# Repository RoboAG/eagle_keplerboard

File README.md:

# keplerboard
Circuit for simple robots.

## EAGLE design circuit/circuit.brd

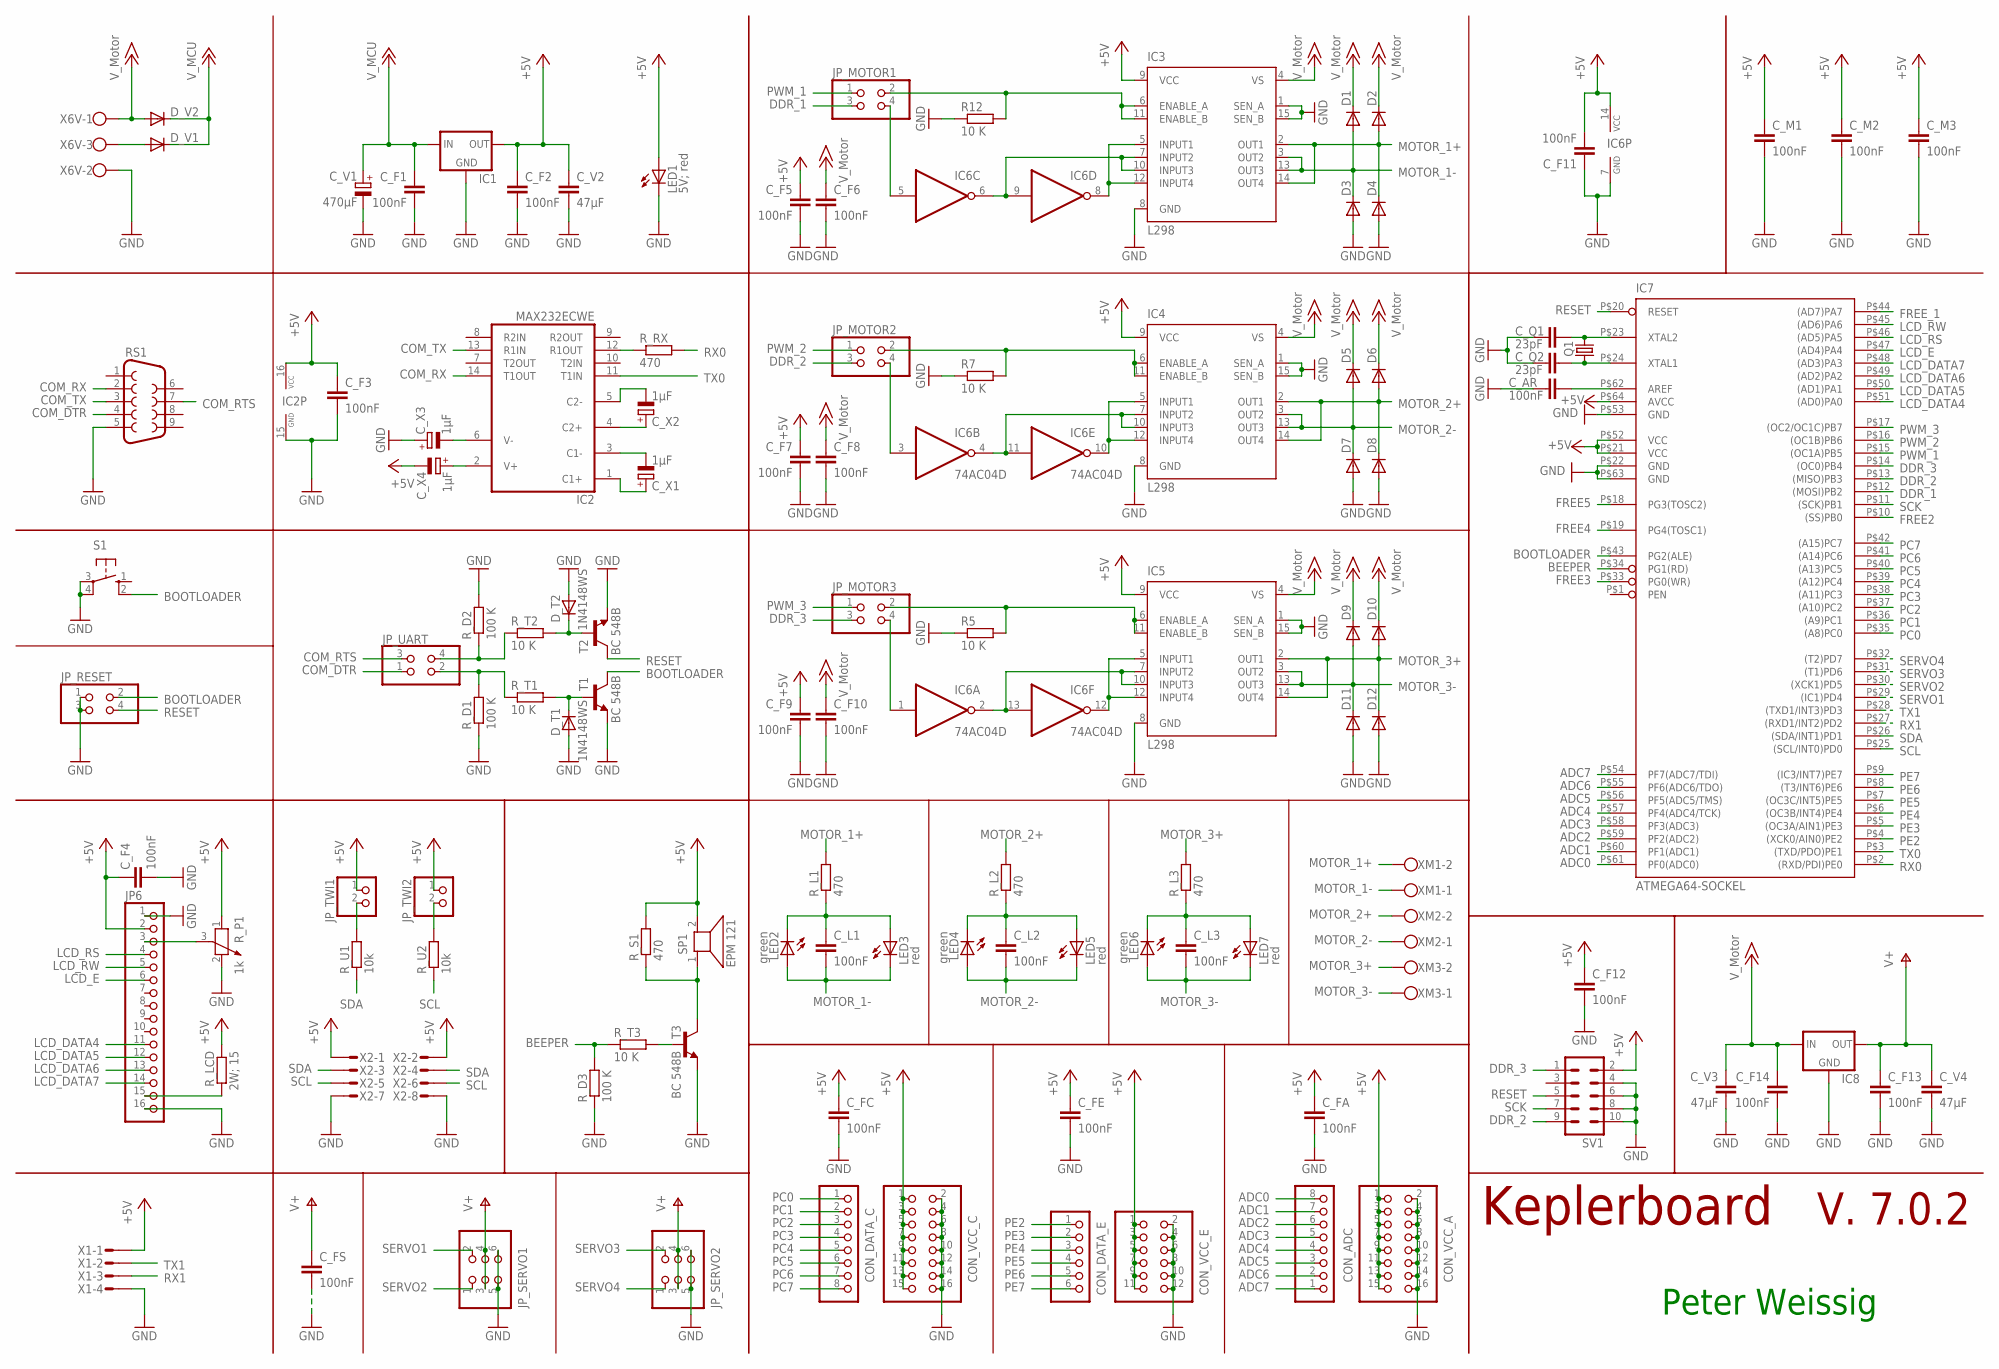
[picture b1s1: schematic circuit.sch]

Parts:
CON_ADC: PINHD-1X8; 1X08
CON_DATA_C: PINHD-1X8; 1X08
CON_DATA_E: PINHD-1X6; 1X06
CON_VCC_A: PINHD-2X8; 2X08
CON_VCC_C: PINHD-2X8; 2X08
CON_VCC_E: PINHD-2X6; 2X06
C_AR: 100nF; C025-025X050
C_F1, C_F2, C_F3, C_F5, C_F6, C_F7, C_F8, C_F9, C_F10, C_F11, C_F12, C_F13, C_F14: 100nF; C1206K
C_F4: 100nF; C025-025X050
C_FA: 100nF; C025-025X050
C_FC: 100nF; C025-025X050
C_FE: 100nF; C025-025X050
C_FS: 100nF; C1206K
C_L1, C_L2, C_L3: 100nF; C1206K
C_M1, C_M2, C_M3: 100nF; C025-025X050
C_Q1, C_Q2: 23pF; C3216
C_V1: 470µF; E5-10,5
C_V2, C_V3, C_V4: 47µF; C1210K
C_X1, C_X2, C_X3, C_X4: 1µF; A/3216-18W
D1, D2, D3, D4, D5, D6, D7, D8, D9, D10, D11, D12: DIODE-SMC; SMC
D_T1, D_T2: 1N4148WS; SOD323-W
D_V1, D_V2: DIODE-SMC; SMC
IC1, IC8: 78XXS
IC2: MAX232ECWE; SO16L
IC3, IC4, IC5: L298; MULTIWATT-15
IC6: 74AC04D; SO14
IC7: ATMEGA64-SOCKEL; SOCKEL_TQFP64
JP6: PINHD-1X16; 1X16
JP_MOTOR1, JP_MOTOR2, JP_MOTOR3: PINHD-2X2; 2X02
JP_RESET: PINHD-2X2; 2X02
JP_SERVO1, JP_SERVO2: PINHD-2X3; 2X03
JP_TWI1, JP_TWI2: PINHD-1X2; 1X02
JP_UART: PINHD-2X2; 2X02
LED1: 5V; red; LED3MM
LED2, LED4, LED6: green; CHIPLED_1206
LED3, LED5, LED7: red; CHIPLED_1206
Q1: CRYSTALHC49UP; HC49UP
R5, R7, R12: 10 K; R1206
RS1: F09H
R_D1, R_D2, R_D3: 100 K; R1206
R_L1, R_L2, R_L3: 470; R1206
R_LCD: 2W; 15; 0414/15
R_P1: 1k; PT-10
R_RX: 470; R1206
R_S1: 470; R1206
R_T1, R_T2, R_T3: 10 K; R1206
R_U1, R_U2: 10k; R1206
S1: TASTER; TASTER_SMD
SP1: EPM 121; AL60P
SV1: ML10
T1, T2, T3: BC 548B; TO92
X1: MICROMATCH-4
X2: MICROMATCH-8
X6V: W237-103
XM1, XM2, XM3: W237-102

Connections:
+5V: CON_VCC_A.1, CON_VCC_A.3, CON_VCC_A.5, CON_VCC_A.7, CON_VCC_A.9, CON_VCC_A.11, CON_VCC_A.13, CON_VCC_A.15, CON_VCC_C.1, CON_VCC_C.3, CON_VCC_C.5, CON_VCC_C.7, CON_VCC_C.9, CON_VCC_C.11, CON_VCC_C.13, CON_VCC_C.15, CON_VCC_E.1, CON_VCC_E.3, CON_VCC_E.5, CON_VCC_E.7, CON_VCC_E.9, CON_VCC_E.11, C_F2.1, C_F3.1, C_F4.1, C_F5.1, C_F7.1, C_F9.1, C_F11.2, C_F12.1, C_FA.1, C_FC.1, C_FE.1, C_M1.1, C_M2.1, C_M3.1, C_V2.1, C_X4.-, IC1.OUT, IC2.16 (VCC), IC3.9 (VCC), IC4.9 (VCC), IC5.9 (VCC), IC6.14 (VCC), IC7.P$21 (VCC), IC7.P$52 (VCC), IC7.P$64 (AVCC), JP6.2, JP_TWI1.1, JP_TWI2.1, LED1.A, R_LCD.1, R_P1.1, R_S1.2, SP1.2, SV1.2, X1.1, X2.1, X2.2
+12V: C_F1.1, C_V1.+, D_V1.C, D_V2.C, IC1.IN
+15V: C_F6.1, C_F8.1, C_F10.1, C_F14.1, C_V3.1, D1.C, D2.C, D5.C, D6.C, D9.C, D10.C, D_V2.A, IC3.4 (VS), IC4.4 (VS), IC5.4 (VS), IC8.IN, X6V.1
ADC0: CON_ADC.8, IC7.P$61 (PF0(ADC0))
ADC1: CON_ADC.7, IC7.P$60 (PF1(ADC1))
ADC2: CON_ADC.6, IC7.P$59 (PF2(ADC2))
ADC3: CON_ADC.5, IC7.P$58 (PF3(ADC3))
ADC4: CON_ADC.4, IC7.P$57 (PF4(ADC4/TCK))
ADC5: CON_ADC.3, IC7.P$56 (PF5(ADC5/TMS))
ADC6: CON_ADC.2, IC7.P$55 (PF6(ADC6/TDO))
ADC7: CON_ADC.1, IC7.P$54 (PF7(ADC7/TDI))
BEEPER: IC7.P$34 (PG1(RD)), R_D3.2, R_T3.1
BOOTLOADER: IC7.P$43 (PG2(ALE)), JP_RESET.2, S1.2 (S1), T1.1 (C)
COM_DTR: JP_UART.1, RS1.4
COM_RTS: JP_UART.3, RS1.7
COM_RX: IC2.14 (T1OUT), RS1.2
COM_TX: IC2.13 (R1IN), RS1.3
DDR_1: IC7.P$12 ((MOSI)PB2), JP_MOTOR1.3
DDR_2: IC7.P$13 ((MISO)PB3), JP_MOTOR2.3, SV1.9
DDR_3: IC7.P$14 ((OC0)PB4), JP_MOTOR3.3, SV1.1
FREE2: IC7.P$10 ((SS)PB0)
FREE3: IC7.P$33 (PG0(WR))
FREE4: IC7.P$19 (PG4(TOSC1))
FREE5: IC7.P$18 (PG3(TOSC2))
FREE_1: IC7.P$44 ((AD7)PA7)
GND: CON_VCC_A.2, CON_VCC_A.4, CON_VCC_A.6, CON_VCC_A.8, CON_VCC_A.10, CON_VCC_A.12, CON_VCC_A.14, CON_VCC_A.16, CON_VCC_C.2, CON_VCC_C.4, CON_VCC_C.6, CON_VCC_C.8, CON_VCC_C.10, CON_VCC_C.12, CON_VCC_C.14, CON_VCC_C.16, CON_VCC_E.2, CON_VCC_E.4, CON_VCC_E.6, CON_VCC_E.8, CON_VCC_E.10, CON_VCC_E.12, C_AR.1, C_F1.2, C_F2.2, C_F3.2, C_F4.2, C_F5.2, C_F6.2, C_F7.2, C_F8.2, C_F9.2, C_F10.2, C_F11.1, C_F12.2, C_F13.2, C_F14.2, C_FA.2, C_FC.2, C_FE.2, C_FS.2, C_M1.2, C_M2.2, C_M3.2, C_Q1.1, C_Q2.1, C_V1.-, C_V2.2, C_V3.2, C_V4.2, C_X3.+, D3.A, D4.A, D7.A, D8.A, D11.A, D12.A, D_T1.A, D_T2.A, IC1.GND, IC2.15 (GND), IC3.1 (SEN_A), IC3.8 (GND), IC3.15 (SEN_B), IC4.1 (SEN_A), IC4.8 (GND), IC4.15 (SEN_B), IC5.1 (SEN_A), IC5.8 (GND), IC5.15 (SEN_B), IC6.7 (GND), IC7.P$22 (GND), IC7.P$53 (GND), IC7.P$63 (GND), IC8.GND, JP6.1, JP6.16, JP_RESET.1, JP_RESET.3, JP_SERVO1.5, JP_SERVO1.6, JP_SERVO2.5, JP_SERVO2.6, LED1.K (C), R5.1, R7.1, R12.1, RS1.5, R_D1.1, R_D2.2, R_D3.1, R_P1.2, S1.3, S1.4 (P1), SV1.4, SV1.6, SV1.8, SV1.10, T1.3 (E), T2.3 (E), T3.3 (E), X1.4, X2.7, X2.8, X6V.2
LCD_DATA4: IC7.P$51 ((AD0)PA0), JP6.11
LCD_DATA5: IC7.P$50 ((AD1)PA1), JP6.12
LCD_DATA6: IC7.P$49 ((AD2)PA2), JP6.13
LCD_DATA7: IC7.P$48 ((AD3)PA3), JP6.14
LCD_E: IC7.P$47 ((AD4)PA4), JP6.6
LCD_RS: IC7.P$46 ((AD5)PA5), JP6.4
LCD_RW: IC7.P$45 ((AD6)PA6), JP6.5
MOTOR_1+: D2.A, D4.C, IC3.2 (OUT1), IC3.14 (OUT4), R_L1.2, XM1.2
MOTOR_1-: C_L1.2, D1.A, D3.C, IC3.3 (OUT2), IC3.13 (OUT3), LED2.A, LED3.C, XM1.1
MOTOR_2+: D6.A, D8.C, IC4.2 (OUT1), IC4.14 (OUT4), R_L2.2, XM2.2
MOTOR_2-: C_L2.2, D5.A, D7.C, IC4.3 (OUT2), IC4.13 (OUT3), LED4.A, LED5.C, XM2.1
MOTOR_3+: D10.A, D12.C, IC5.2 (OUT1), IC5.14 (OUT4), R_L3.2, XM3.2
MOTOR_3-: C_L3.2, D9.A, D11.C, IC5.3 (OUT2), IC5.13 (OUT3), LED6.A, LED7.C, XM3.1
unnamed: IC6.3 (I), JP_MOTOR2.4
unnamed: IC4.7 (INPUT2), IC4.10 (INPUT3), IC6.4 (O), IC6.11 (I)
unnamed: JP_TWI1.2, R_U1.2
unnamed: R_S1.1, SP1.1, T3.1 (C)
unnamed: R_T3.2, T3.2 (B)
unnamed: JP6.3, R_P1.3
unnamed: C_AR.2, IC7.P$62 (AREF)
unnamed: IC4.6 (ENABLE_A), IC4.11 (ENABLE_B), JP_MOTOR2.2, R7.2
unnamed: JP_TWI2.2, R_U2.2
unnamed: D_V1.A, X6V.3
unnamed: IC4.5 (INPUT1), IC4.12 (INPUT4), IC6.10 (O)
unnamed: C_Q1.2, IC7.P$23 (XTAL2), Q1.2
unnamed: C_L1.1, LED2.C, LED3.A, R_L1.1
unnamed: C_Q2.2, IC7.P$24 (XTAL1), Q1.1
unnamed: IC5.5 (INPUT1), IC5.12 (INPUT4), IC6.12 (O)
unnamed: IC6.5 (I), JP_MOTOR1.4
unnamed: IC3.5 (INPUT1), IC3.12 (INPUT4), IC6.8 (O)
unnamed: IC3.7 (INPUT2), IC3.10 (INPUT3), IC6.6 (O), IC6.9 (I)
unnamed: IC6.1 (I), JP_MOTOR3.4
unnamed: JP6.15, R_LCD.2
unnamed: D_T2.C, R_T2.2, T2.2 (B)
unnamed: IC5.7 (INPUT2), IC5.10 (INPUT3), IC6.2 (O), IC6.13 (I)
unnamed: C_L3.1, LED6.C, LED7.A, R_L3.1
unnamed: C_L2.1, LED4.C, LED5.A, R_L2.1
unnamed: D_T1.C, R_T1.2, T1.2 (B)
unnamed: C_X4.+, IC2.2 (V+)
unnamed: C_X3.-, IC2.6 (V-)
unnamed: C_X2.+, IC2.4 (C2+)
unnamed: C_X1.+, IC2.1 (C1+)
unnamed: C_X1.-, IC2.3 (C1-)
unnamed: C_X2.-, IC2.5 (C2-)
unnamed: JP_UART.2, R_D1.2, R_T1.1
unnamed: JP_UART.4, R_D2.1, R_T2.1
unnamed: IC2.12 (R1OUT), R_RX.1
PC0: CON_DATA_C.1, IC7.P$35 ((A8)PC0)
PC1: CON_DATA_C.2, IC7.P$36 ((A9)PC1)
PC2: CON_DATA_C.3, IC7.P$37 ((A10)PC2)
PC3: CON_DATA_C.4, IC7.P$38 ((A11)PC3)
PC4: CON_DATA_C.5, IC7.P$39 ((A12)PC4)
PC5: CON_DATA_C.6, IC7.P$40 ((A13)PC5)
PC6: CON_DATA_C.7, IC7.P$41 ((A14)PC6)
PC7: CON_DATA_C.8, IC7.P$42 ((A15)PC7)
PE2: CON_DATA_E.1, IC7.P$4 ((XCK0/AIN0)PE2)
PE3: CON_DATA_E.2, IC7.P$5 ((OC3A/AIN1)PE3)
PE4: CON_DATA_E.3, IC7.P$6 ((OC3B/INT4)PE4)
PE5: CON_DATA_E.4, IC7.P$7 ((OC3C/INT5)PE5)
PE6: CON_DATA_E.5, IC7.P$8 ((T3/INT6)PE6)
PE7: CON_DATA_E.6, IC7.P$9 ((IC3/INT7)PE7)
PWMM1: IC3.6 (ENABLE_A), IC3.11 (ENABLE_B), JP_MOTOR1.2, R12.2
PWMM3: IC5.6 (ENABLE_A), IC5.11 (ENABLE_B), JP_MOTOR3.2, R5.2
PWM_1: IC7.P$15 ((OC1A)PB5), JP_MOTOR1.1
PWM_2: IC7.P$16 ((OC1B)PB6), JP_MOTOR2.1
PWM_3: IC7.P$17 ((OC2/OC1C)PB7), JP_MOTOR3.1
RESET: IC7.P$20 (RESET), JP_RESET.4, SV1.5, T2.1 (C)
RX0: IC7.P$2 ((RXD/PDI)PE0), R_RX.2
RX1: IC7.P$27 ((RXD1/INT2)PD2), X1.3
SCK: IC7.P$11 ((SCK)PB1), SV1.7
SCL: IC7.P$25 ((SCL/INT0)PD0), R_U2.1, X2.5, X2.6
SDA: IC7.P$26 ((SDA/INT1)PD1), R_U1.1, X2.3, X2.4
SERVO1: IC7.P$29 ((IC1)PD4), JP_SERVO1.2
SERVO2: IC7.P$30 ((XCK1)PD5), JP_SERVO1.1
SERVO3: IC7.P$31 ((T1)PD6), JP_SERVO2.2
SERVO4: IC7.P$32 ((T2)PD7), JP_SERVO2.1
TX0: IC2.11 (T1IN), IC7.P$3 ((TXD/PDO)PE1)
TX1: IC7.P$28 ((TXD1/INT3)PD3), X1.2
V+: C_F13.1, C_FS.1, C_V4.1, IC8.OUT, JP_SERVO1.3, JP_SERVO1.4, JP_SERVO2.3, JP_SERVO2.4

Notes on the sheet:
Keplerboard
V. 7.0.2
Peter Weissig

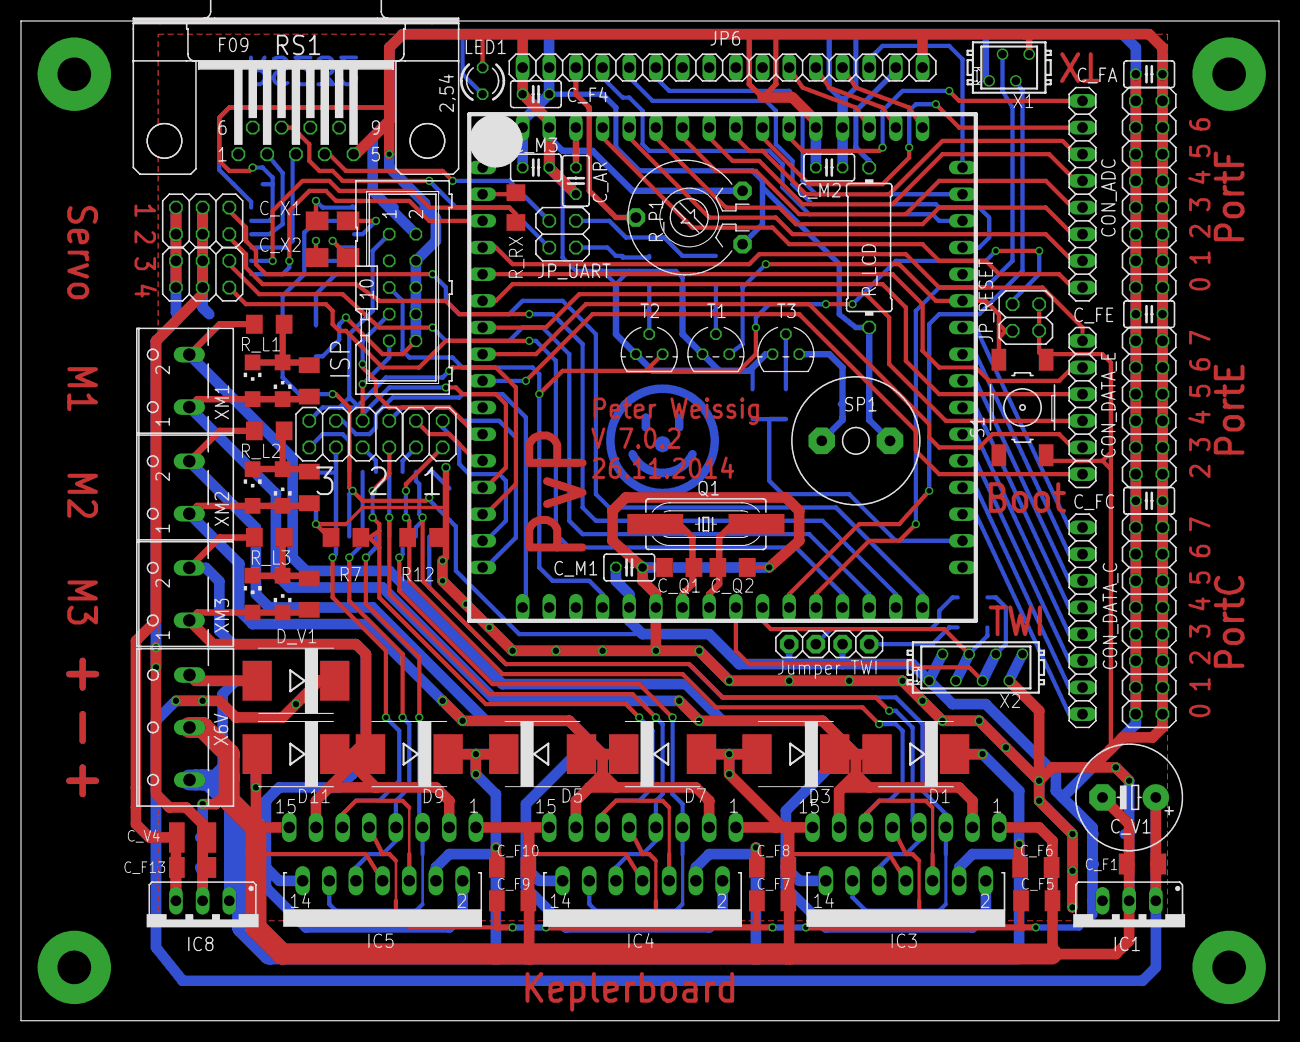
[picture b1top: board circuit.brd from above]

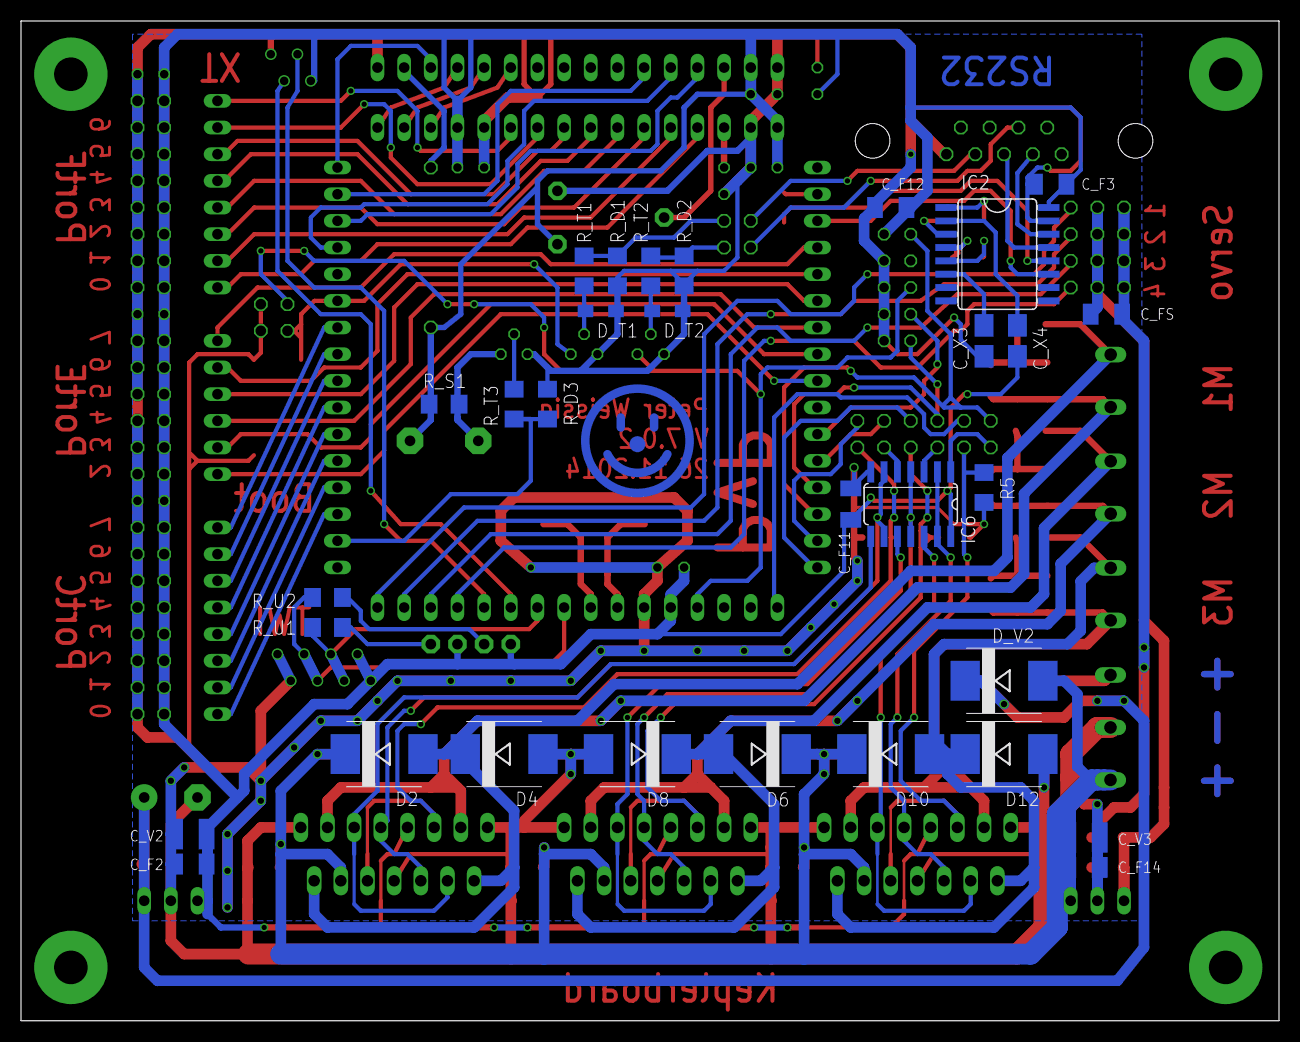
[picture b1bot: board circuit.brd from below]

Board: 2 copper layers, 119.8 x 95.2 mm, 114 parts (31 on the bottom side), 100 nets.

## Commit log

2015-09-28 updated to version 2.0
2015-09-28 added todo list
2015-09-29 updated file "TODO" - error in schematics - ISP doesn't work
2015-10-05 added bugfix (wrong lines for isp-programming) for Version 7.0.2
2015-10-05 update TODO according to bugfix
2015-10-05 update bugfix for isp programmer (images)
2017-11-26 updated LICENSE, TODO and added parts.ods
2019-06-22 added bug of wrong labelled PORTE (thanks to Janek for reporting)
